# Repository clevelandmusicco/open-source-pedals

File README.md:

# Cleveland Music Co. Open Source Pedals

Here you can find the design files used in the production of [Cleveland Music Co.](https://clevelandmusicco.com) pedals. This includes schematics, PCB layouts, Gerber/BOM/CPL files for PCB fabrication and assembly, templates for enclosure drilling, and more. In addition to the sources we use for our retail pedals and kits, there are several DIY projects for popular so-called "clones" you can modify and/or fabricate on your own. All of these materials are made available as [Open Source Hardware](https://oshwa.org/resources/open-source-hardware-definition/) distributed under a [Creative Commons Attribution-ShareAlike 4.0 International license](https://creativecommons.org/licenses/by-sa/4.0/).

&nbsp;&nbsp;&nbsp;&nbsp;&nbsp;&nbsp;&nbsp;&nbsp;&nbsp;&nbsp;

## What is here and how do I view or use it?

The directory structure is self-explanatory.

* Most schematics and PCB layouts were created with [Eagle 9.6.2](https://eagle-updates.circuits.io/downloads/latest.html), which is free for personal use (but not open source). Designs added in the future will likely be created in [KiCad](https://www.kicad.org/).
* The zipped Gerber files, BOM, and CPL files can be used as-is at [JLCPCB](https://jlcpcb.com/).
* Drill layouts for enclosures are formatted for use and stored at [Tayda Electronics](https://drill.taydakits.com/).

If there are any deviations from the above, the README file for each pedal points that out.

>[!IMPORTANT]
>All Cleveland Music Co. logos and trademarks have been removed from these source files. The artwork we use for our commercial products is also omitted. This is conventient because it creates a clean starting point for modification, but it also helps to avoid potential branding conflicts or confusion. 
>
>Use of Cleveland Music Co. trademarks, logos, or other branding on any hardware, software, or documentation (including design files) derived from these materials without express written consent from Cleveland Music Co. is not permitted. 

### `eagle` directory files

The `.sch` and `.brd` (schematic and board) files are included. Additionally, there is an `.lbr` (library) containing only the footprints required to view and manipulate the `.brd` layout.

**The PCB layouts mostly use SMD components, with a few exceptions:** As a rule of thumb, aluminum electrolytic capacitors used for power filtering are through-hole, as are potentiometers, LEDs, switches, and trimmers. Some designs include through-hole pads for silver mica "tone capacitors" or similiar. This is pointed out in each pedal's README file and component suggestions are provided.

_The Superior Overdrive `.brd` file loaded in Eagle. Note the Cleveland Music Co. branding and trademarks have been removed from the source files._

### `fabrication` directory files

The `.zip` containing Gerber files is ready-to-use at [JLCPCB](https://jlcpcb.com/). It might be compatible with other services, but we haven't tested it. Also included are verified and tested `BOM.csv` and `CPL.csv` files for PCBA (Printed Circuit Board Assembly) services at JLCPCB.

The BOMs follow a few general guidelines:

1. High-quality component manufacturers like TDK, onsemi, Texas Instruments, Murata, Samsung, and others are favored wherever possible.
2. Audio signal path capacitors use C0G or NP0 MLCC capacitors from JLCPCB's parts library wherever possible.
3. As C0G/NP0 SMD capacitors tend to be larger than their X7R equivalents, 1206 and 0805 footprints are common for audio signal path capacitors in the PCB layouts.
4. Some of the BOMs can get expensive at JLCPCB due to the use of many so-called ["extended" components](https://jlcpcb.com/help/article/pcb-assembly-faqs). Our retail pedals and kits always use the highest-quality available components where it makes sense. If you want less expensive PCBs, use less expensive "basic" parts from the JLCPCB parts library, or source and solder the components yourself.

_Rendering of a Cleveland Music Co. Superior Overdrive PCB fabricated with these files. Note the Cleveland Music Co. branding and trademarks have been removed from the source files._

There is also a `.url` file with a link to the Drill Template at Tayda. These templates have been verified and tested. For example, [here is the Superior Overdrive Drill Template](https://drill.taydakits.com/box-designs/new?public_key=SVhxKzdDNXZjeXVUNXpSM1phNTFkdz09Cg==).

_The Superior Overdrive Drill Template at Tayda Electronics._

## What is [Open Source Hardware](https://oshwa.org/resources/open-source-hardware-definition/)?

Open source hardware is hardware whose design is made publicly available so that anyone can study, modify, distribute, make, and sell the design or hardware based on that design. The hardware’s source, the design from which it is made, is available in the preferred format for making modifications to it. Ideally, open source hardware uses readily-available components and materials, standard processes, open infrastructure, unrestricted content, and open-source design tools to maximize the ability of individuals to make and use hardware. Open source hardware gives people the freedom to control their technology while sharing knowledge and encouraging commerce through the open exchange of designs.

## In a nutshell, what is the [Creative Commons Attribution-ShareAlike 4.0 International license](https://creativecommons.org/licenses/by-sa/4.0/)?

### You are free to:

* **Share** — copy and redistribute the material in any medium or format for any purpose, even commercially.
* **Adapt** — remix, transform, and build upon the material for any purpose, even commercially.

### Under the following terms:

* **Attribution** — You must give appropriate credit, provide a link to the license, and indicate if changes were made. You may do so in any reasonable manner, but not in any way that suggests Cleveland Music Co. endorses you or your use.
* **ShareAlike** — If you remix, transform, or build upon the material, you must distribute your contributions under the same license as the original.
* **No additional restrictions** — You may not apply legal terms or technological measures that legally restrict others from doing anything the license permits.

We cannot revoke these freedoms as long as you follow the license terms, even if we decide to stop distributing these materials under the terms at a later date.

>[!WARNING]
>No warranties are given. The license may not give you all of the permissions necessary for your intended use. For example, other rights such as publicity, privacy, or moral rights may limit how you use these materials.

>[!CAUTION]
>This description highlights only some of the key features and terms of [the actual license](https://creativecommons.org/licenses/by-sa/4.0/). It is not a license and has no legal value. You should carefully review all of the terms and conditions of [the actual license](https://creativecommons.org/licenses/by-sa/4.0/) before using the contents of this repository.

## Why would a for-profit company do this? Are you worried about people "ripping you off"?

Basically, two ideas we fiercely support:

1. Sharing designs promotes innovation. Designers don't waste brain power "reinventing the wheel" when they can freely reuse and improve upon public designs.
2. People should have the right to study, modify, AND REPAIR the physical devices they own. And if people do not or cannot buy our hardware products for any reason, the should have _permission_ to make, sell, and distribute new designs or hardware derived from ours, as long as their work is also publicly shared.

We're not worried about people "ripping us off". Practically speaking, even with access to a product’s design, it's not trivial for someone else to make and sell it. They still need to source components, manufacture and/or assemble parts, design and implement a testing strategy, create distribution and commerce channels, and much more. We have a head start doing all of this while offering our products at prices low enough that it's likely not worth undercutting us. And frankly, if people really wanted to rip us off, they would reverse engineer and reproduce our products _whether they were open source or not_, selling them at higher "prestige" prices. Legally speaking, this would not make them criminals; it would just make them assholes.

So, as a matter of principle, we're happy to accept the risks posed by bad actors as the price to make knowledge and freedoms available to the good ones (such as yourself).

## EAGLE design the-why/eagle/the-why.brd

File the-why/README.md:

# The 'Why'

The 'Why' is an adaptation of the venerable Electro-Harmonix (EHX) Big Muff circuit. All components are surface mount (SMD) except for the power filtering capacitor and three board-mounted pots. So, assembly is as simple as soldering these four parts to the PCB.

## Big Muff Circuit Variation

The Big Muff is famous for its many different variants over the years, each having a unique sound due to its mix of component values, transistor types and current gain (hFE), and even the dielectrics of the capacitors. Since the topology of the schematic is consistent, the same PCB layout can be used to make (almost) any variant. So, fabricating a "Ram's Head" as opposed to a "Green Russian", for example, is a matter of editing the BOM. I have made no fewer than five great-sounding Big Muffs using the files in this directory, with some of them being mashups of values from several different variants (the [Cleveland Music Co. Smuffle Fuzz](https://clevelandmusicco.com/pedals/smuffle-fuzz/) is one such example).

The canonical source for Big Muff schematics has to be [Kit Rae's Big Muff Page](https://www.kitrae.net/music/music_big_muff.html). Here you can find a schematic for every known variant of the Big Muff circuit with consistent part identifiers and notes about capacitor dialectrics, transistors, etc.

To make it easy to fab different variants, I have used the same identifiers Kit uses on his website. The schematic in the `eagle` directory is from [the David Gilmour Big Muff](https://www.kitrae.net/music/David_Gilmour_Big_Muff.html) (which Kit calls "Version 2 Big Muff 1973 #3"), and `BOM_gilmour.csv` specifies JLC part numbers that match this schematic. It sounds really, really good. If you want to make a different variant, simply create a new BOM selecting parts that match the schematic of you choice.

`BOM_gilmour.csv` specifies fairly low-hFE [MMBT3904 transistors](https://jlcpcb.com/partdetail/21237-MMBT3904_RANGE_100_300/C20526). I think they sound great in this variant, but hFE on Big Muff transistors varies wildly. Do some reading at Kit's page and tweak as you see fit.

>[!NOTE]
> I'll add more BOMs in the future; especially the variants that are most often cloned. Pull requests are also welcome! The only reason I haven't added more already is that most of mine use parts that aren't in the public JLC Parts Library ¯\\_(ツ)_/¯

You may occasionally need to change a capacitor footprint to use the part number you want (the 0603 C8 is probably the leading candidate here; I happen to have a large number of C0G 0603 caps in my personal parts library). The largest footprint in `the-why.lbr` is 1206; there's plenty of space on the board to make all capacitors 1206 if you wanted to. You won't even need to change the CPL coordinates if you're careful.

## Through-hole Component Suggestions

| Qty | URL | Description | Notes |
| --- | --- | --- | --- |
| 3 | [Tayda SKU A-2907](https://www.taydaelectronics.com/b-100k-ohm-linear-taper-potentiometer-with-pc-mount.html) | B100K OHM Linear Taper Potentiometer PC Mount | I typically use A100K for SUSTAIN and VOLUME |
| 1 | [Mouser PN 667-EEU-FR1E101B](https://www.mouser.com/ProductDetail/667-EEU-FR1E101B) | Use whatever low-ESR cap you prefer |

## A Few Words About SMD/SMT Hate

Get over it. If you want to make an exact clone of a 1969 Big Muff Pi V1, best of luck to you; The 'Why' is probably not a project for you. The 'Why' _is_ for Muffheads who want to learn about SMT PCBA, are intrigued or at least aren't bothered by it, or just can't be arsed to source and solder through-hole components.

Sure, SMT is more difficult (if not impossible) to repair sometimes. And, yeah, such tiny parts must _sound different_ than big, magical, 'mojo' parts, right? Of course they do. But the same could be said for every part in every version of the Big Muff that ever used different capacitor dielectrics or resistor material or paint colour or whatever. An NP0 MLCC SMD capacitor performs differently than a polyester film cap. Obviously. But different isn't the same as inferior.

Also consider that component tolerances can make ten Big Muffs that came off the line back-to-back in 1974 all sound slightly different, even when brand new. Going by the values on a schematic will not get you an exact copy of the holy grail sound you might think you're seeking. Many of the critical components used were often well out of the specified tolerance in the first place, and as the parts age, those values drift even further.

(Let's not talk about 'fidelity', either. The purpose of distortion devices like the Big Muff is literally to _distort (pull or twist out of shape)_ an audio signal. Come on, man.)

So, if you know what you're doing and you select capacitor dielectrics that make sense, pay attention to transistor current gain, and so on, you can make a perfectly-legitimate, excellent-sounding (and often far less noisy) Big Muff with SMT.

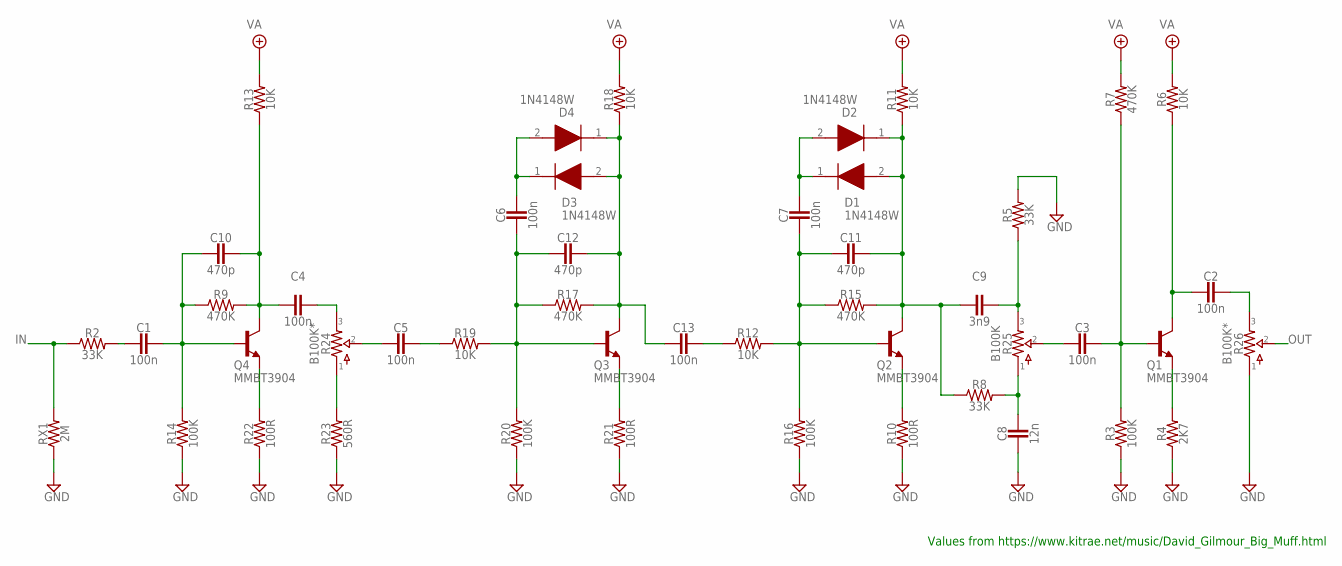
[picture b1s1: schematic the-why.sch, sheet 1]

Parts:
C1, C2, C3, C4, C5, C6, C7, C13: 100n; RESISTOR_C1206
C8: 12n; RESISTOR_R0603
C9: 3n9; RESISTOR_C1206
C10, C11, C12: 470p; RESISTOR_R0603
D1, D2, D3, D4: 1N4148W; SODFL3816X120N
Q1, Q2, Q3, Q4: MMBT3904; TRANSISTOR_SOT23-BEC
R2, R5, R8: 33K; RESISTOR_R0603
R3, R14, R16, R20: 100K; RESISTOR_R0603
R4: 2K7; RESISTOR_R0603
R6, R11, R12, R13, R18, R19: 10K; RESISTOR_R0603
R7, R9, R15, R17: 470K; RESISTOR_R0603
R10, R21, R22: 100R; RESISTOR_R0603
R23: 560R; RESISTOR_R0603
R24, R26: B100K*; 16MM_B.MOUNT
R25: B100K; 16MM_B.MOUNT
RX1: 2M; RESISTOR_R0603

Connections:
GND: C8.2, R3.1, R4.1, R5.2, R10.1, R14.1, R16.1, R20.1, R21.1, R22.1, R23.1, R26.1, RX1.1; also elsewhere on the board
IN: R2.1, RX1.2; also elsewhere on the board
unnamed: C1.2, R2.2
unnamed: C1.1, C10.2, Q4.B, R9.1, R14.2
unnamed: C4.2, C10.1, Q4.C, R9.2, R13.1
unnamed: Q4.E, R22.2
unnamed: C4.1, R24.3
unnamed: R23.2, R24.1
unnamed: C5.2, R24.2
unnamed: C5.1, R19.1
unnamed: C6.2, C12.2, Q3.B, R17.1, R19.2, R20.2
unnamed: C6.1, D3.1 (K), D4.2 (A)
unnamed: Q3.E, R21.2
unnamed: C9.1, R5.1, R25.3
unnamed: C13.1, R12.1
unnamed: C7.2, C11.2, Q2.B, R12.2, R15.1, R16.2
unnamed: Q2.E, R10.2
unnamed: C7.1, D1.1 (K), D2.2 (A)
unnamed: C8.1, R8.2, R25.1
unnamed: C3.2, R25.2
unnamed: C3.1, Q1.B, R3.2, R7.1
unnamed: Q1.E, R4.2
unnamed: C2.2, Q1.C, R6.1
unnamed: C2.1, R26.3
unnamed: C12.1, C13.2, D3.2 (A), D4.1 (K), Q3.C, R17.2, R18.1
unnamed: C9.2, C11.1, D1.2 (A), D2.1 (K), Q2.C, R8.1, R11.1, R15.2
OUT: R26.2; also elsewhere on the board
VA: R6.2, R7.2, R11.2, R13.2, R18.2; also elsewhere on the board

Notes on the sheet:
Values from https://www.kitrae.net/music/David_Gilmour_Big_Muff.html

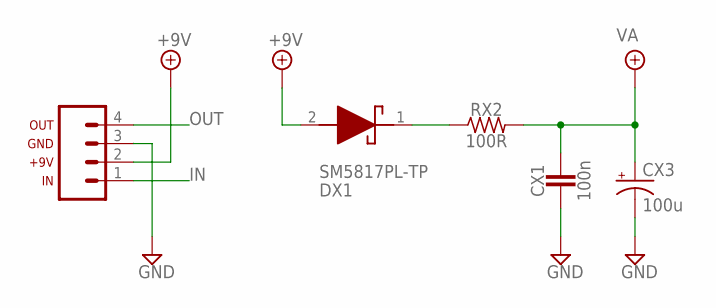
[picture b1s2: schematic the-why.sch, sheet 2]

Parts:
CX1: 100n; RESISTOR_R0603
CX3: 100u; 063_025
DX1: SM5817PL-TP; SOD3716X120N
J101: 1X04_SMD_STRAIGHT_COMBO; 1X04
RX2: 100R; RESISTOR_R0603

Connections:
+9V: DX1.2 (A), J101.2 (+9V)
GND: CX1.2, CX3.-, J101.3 (GND); also elsewhere on the board
IN: J101.1 (IN); also elsewhere on the board
unnamed: DX1.1 (K), RX2.1
OUT: J101.4 (OUT); also elsewhere on the board
VA: CX1.1, CX3.+, RX2.2; also elsewhere on the board

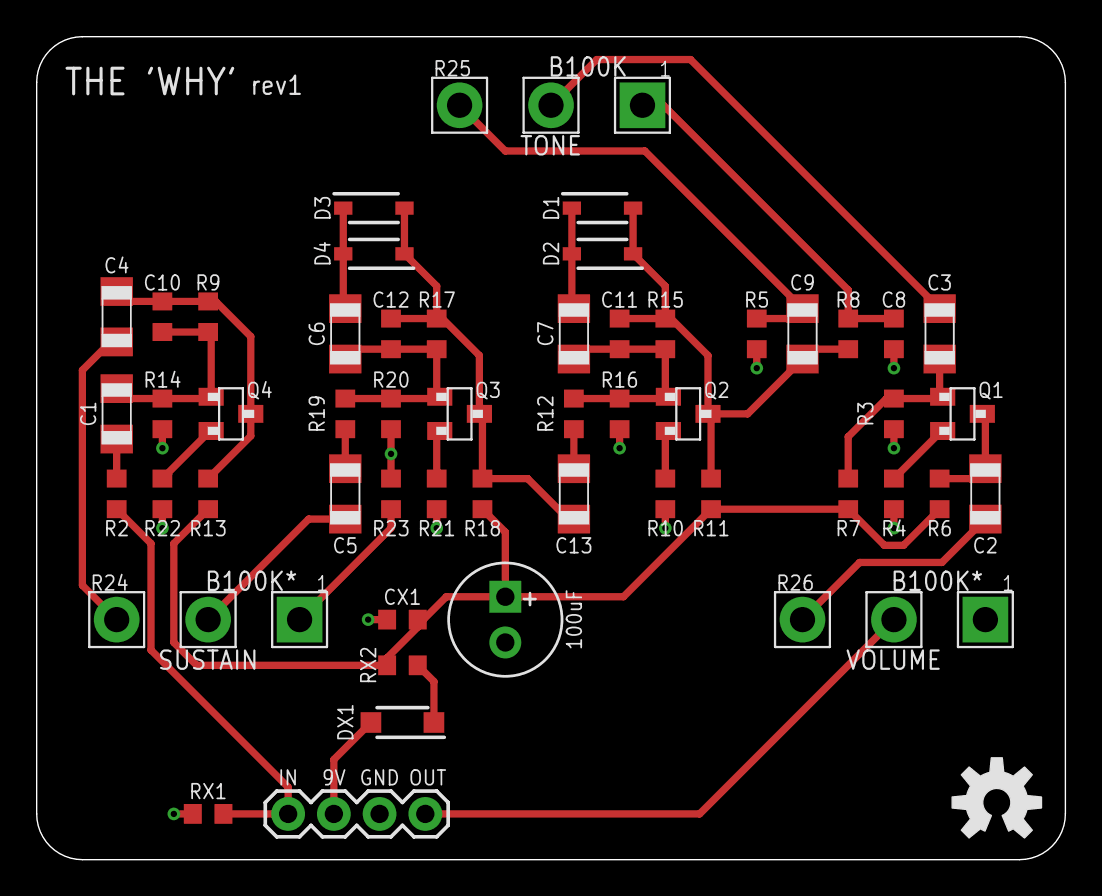
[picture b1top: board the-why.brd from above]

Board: 2 copper layers, 57.1 x 45.7 mm, 54 parts (0 on the bottom side), 30 nets.

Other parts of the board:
U$1: 125B_BOARD
U$2: OSHW-LOGO-M

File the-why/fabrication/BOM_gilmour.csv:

Comment,Designator,Footprint,JLCPCB Part #（optional）
100n,C1,CAP_C1206,C338082
100n,C2,CAP_C1206,C338082
100n,C3,CAP_C1206,C338082
100n,C4,CAP_C1206,C338082
100n,C5,CAP_C1206,C338082
100n,C6,CAP_C1206,C338082
100n,C7,CAP_C1206,C338082
12n,C8,CAP_C0603,C2178767
3n9,C9,CAP_C1206,C541503
470p,C10,CAP_C0603,C27694
470p,C11,CAP_C0603,C27694
470p,C12,CAP_C0603,C27694
100n,C13,CAP_C1206,C338082
100n,CX1,CAP_C0603,C14663
1N4148W,D1,SODFL3816X120N,C81598
1N4148W,D2,SODFL3816X120N,C81598
1N4148W,D3,SODFL3816X120N,C81598
1N4148W,D4,SODFL3816X120N,C81598
SM5817PL-TP,DX1,SOD3716X120N,C7420328
MMBT3904,Q1,TRANSISTOR_SOT23-BEC,C20526
MMBT3904,Q2,TRANSISTOR_SOT23-BEC,C20526
MMBT3904,Q3,TRANSISTOR_SOT23-BEC,C20526
MMBT3904,Q4,TRANSISTOR_SOT23-BEC,C20526
33K,R2,RESISTOR_R0603,C4216
100K,R3,RESISTOR_R0603,C25803
2K7,R4,RESISTOR_R0603,C13167
33K,R5,RESISTOR_R0603,C4216
10K,R6,RESISTOR_R0603,C25804
470K,R7,RESISTOR_R0603,C23178
33K,R8,RESISTOR_R0603,C4216
470K,R9,RESISTOR_R0603,C23178
100R,R10,RESISTOR_R0603,C22775
10K,R11,RESISTOR_R0603,C25804
10K,R12,RESISTOR_R0603,C25804
10K,R13,RESISTOR_R0603,C25804
100K,R14,RESISTOR_R0603,C25803
470K,R15,RESISTOR_R0603,C23178
100K,R16,RESISTOR_R0603,C25803
470K,R17,RESISTOR_R0603,C23178
10K,R18,RESISTOR_R0603,C25804
10K,R19,RESISTOR_R0603,C25804
100K,R20,RESISTOR_R0603,C25803
100R,R21,RESISTOR_R0603,C22775
100R,R22,RESISTOR_R0603,C22775
560R,R23,RESISTOR_R0603,C23204
2M,RX1,RESISTOR_R0603,C22976
100R,RX2,RESISTOR_R0603,C22775

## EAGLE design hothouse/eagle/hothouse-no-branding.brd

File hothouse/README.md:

# Hothouse Digital Signal Processing Pedal (125B)

The Hothouse is a compact effect pedal for the [Electrosmith Daisy Seed](https://electro-smith.com/products/daisy-seed). You can use it to easily get Daisy Seed DSP projects off the breadboard and onto your pedalboard, either by compiling and flashing any of the code in [the official repository](https://github.com/clevelandmusicco/HothouseExamples), or by using the [Daisy Web Programmer](https://electro-smith.github.io/Programmer/) with the [pre-compiled binaries](https://github.com/clevelandmusicco/HothouseExamples/releases). And of course, you can also [write your own DSP code for the Hothouse](https://github.com/clevelandmusicco/HothouseExamples/wiki/Creating-your-own-effects). Basically, anything that runs on the Daisy Seed will run on the Hothouse.

This directory contains the open source hardware files for the [Cleveland Music Co. Hothouse DSP Pedal Kit](https://clevelandmusicco.com/hothouse-diy-digital-signal-processing-platform-kit/). Included are the gerber, BOM, and CPL files required to fabricate your own PCBs at JLCPCB. Also included are suggestions for the various through-hole components and other hardware required.

>[!NOTE]
> No step-by-step tutorial for having the boards fabricated is provided. It's assumed that anyone interested in using these files is already familiar with the fabrication process at their provider of choice. However, the files in this repo have only been tested with JLCPCB.

>[!IMPORTANT]
> Remember that all of these materials are made available as [Open Source Hardware](https://oshwa.org/resources/open-source-hardware-definition/) distributed under a [Creative Commons Attribution-ShareAlike 4.0 International license](https://creativecommons.org/licenses/by-sa/4.0/). Before using these materials, be sure to follow the links above and read the [main repo README](/README.md) and [LICENSE](/LICENSE) files.

## Overview

The Hothouse design is comprised of three PCBs:

1. The Main PCB,
2. A Switching & LED daughterboard,
3. A Power & Audio I/O daughterboard.

_The Main PCB_

_The Switching & LED Daughterboard_

_The Power & Audio I/O Daughterboard_

The main PCB is designed for a mix of through-hole and surface-mount components, while the two daughterboards use only through-hole components. The three PCBs are connected by 6-pin ribbon cables. Refer to [the commercial product build docs](https://github.com/clevelandmusicco/HothouseExamples/wiki/Cleveland-Music-Co.-Hothouse-DIY-Digital-Signal-Processing-Pedal-Kit-Build-Guide-(Stereo-Version)) for more information.

All commercial branding (Cleveland Music Co.-specific stuff) has been removed from the PCBs and files in this repository.

### eagle Directory

For each of the three boards, you will find four files:

* An Eagle schematic (`.sch`)
* An Eagle board (`.brd`)
* An Eagle library (`.lbr`) for the devices and footprints specific to the board layout
* A PDF schematic

All the files were created with Eagle 9.6.2 "free". Having separate files for each board provides flexibility; not everyone will want to modify or fab all three PCBs.

### fabrication Directory

There is a zip of the gerber files for each board following the same naming convention as the `eagle` directory. A BOM and CPS file in `.csv` and `.xls` formats is provided for use with `hothouse-no-branding.zip`. You'll also find a DIY drill template in `.pdf` format for those wanting to drill their own 125B enclosures.

## Resources

* [HothouseExamples GitHub repo](https://github.com/clevelandmusicco/HothouseExamples) - The official code examples repo with effects created in C++, Puredata/Plugdata, and Max.
* [Cleveland Music Co. Hothouse DSP Pedal Kit](https://clevelandmusicco.com/hothouse-diy-digital-signal-processing-platform-kit/) - A retail example of a pedal created from the files in this directory. _The chicken or the egg?_ and all that ...
* [Cleveland Music Co. Hothouse Build Guide](https://github.com/clevelandmusicco/HothouseExamples/wiki/Cleveland-Music-Co.-Hothouse-DIY-Digital-Signal-Processing-Pedal-Kit-Build-Guide-(Stereo-Version)) - The build documentation for the retail kit.
* [DIY 125B enclosure drill template](fabrication/hothouse-drill-template.pdf) - For those wanting to drill their own 125B enclosures. It assumes you assemble everything according to the build guide above for proper fit.
* [Tayda 125B drill template](https://drill.taydakits.com/box-designs/new?public_key=Q2luT1FRTVZRM3Bab01YbXd3eituUT09Cg==) - For custom-machined enclosures from Tayda. Highly-recommended if you don't have a drill press or some other way to accurately drill holes in the TOP and SIDES of an enclosure. (You'll need to sign up for an account; FWIW, I've never recieved a single spam email from them.)

## Bill Of Materials

`BOM.xls` (or `BOM.csv`) specifies the surface-mount components. It is adapted from a late-2025 fabrication run used for the commercial kits. "Adapted" because some of the parts used aren't always in stock at JLCPCB publicly (they are stocked in my personal parts library); several components have been swapped out here for purposes of general availability.

Budget-friendly through-hole components to complete the build and some sourcing suggestions:

| QTY | SOURCE URL | DESCRIPTION | NOTES |
| :---: | :--- | :--- | :--- |
| 2 | [Tayda SKU: A-1310](https://www.taydaelectronics.com/20-pin-2-54-mm-single-row-female-pin-header.html) | 20 Pin 2.54mm Single Row Female Pin Header | |
| 3 | [Tayda SKU: A-3670](https://www.taydaelectronics.com/mini-toggle-switch-1m-series-spdt-on-off-on-short-lever.html) | Toggle SPDT On-Off-On Short Lever | |
| 2 | [Tayda SKU: A-4807](https://www.taydaelectronics.com/spst-momentary-soft-touch-push-button-stomp-foots-pedal-switch-on-off-b.html) | SPST Momentary Soft-Touch Push-Button Stomp Switch OFF-(ON) | |
| 6 | [Tayda SKU: A-2969](https://www.taydaelectronics.com/b10k-ohm-linear-taper-potentiometer-round-shaft-pc-mount-l.html) | 10K OHM Linear Taper Potentiometer PCB Mount Round Shaft Dia: 6.35mm | Use whatever 16mm pot you prefer |
| 3 | [Tayda SKU: A-5527](https://www.taydaelectronics.com/dust-seal-covers-for-potentiometer.html) | Dust Seal Cover For Potentiometer | Could also use electrical tape |
| 2 | [Tayda SKU: A-261](https://www.taydaelectronics.com/led-3mm-red.html) | LED 3mm Red | |
| 1 | [Tayda SKU: A-4118](https://www.taydaelectronics.com/dc-power-jack-2-1mm-barrel-type-pcb-mount.html) | DC Power Jack 2.1mm Barrel-Type PCB Mount | The retail kits use a Kobiconn jack, but this works fine |
| 6 | [Tayda SKU: A-932](https://www.taydaelectronics.com/91640-dup-knob-davies-1900h-clone-black.html) | Knob DAVIES 1900H CLONE Black | Or anything that fits the shafts of the pots you're using |
| 1 | [Tayda SKU: A-6628](https://www.taydaelectronics.com/matte-white-sand-texture-125b-style-aluminum-diecast-enclosure.html) | 125B Style Aluminum Diecast Enclosure MATTE WHITE SAND TEXTURE | Colour or finish isn't important; this is just what the retail kits use |
| 1 | [Tayda SKU: A-5165-CST-DR1](https://www.taydaelectronics.com/125b-custom-drill-enclosure-service.html) | 125B ENCLOSURE CUSTOM DRILL SERVICE | Optional |
| 1 | [Tayda SKU: A-5165-CST-UV1](https://www.taydaelectronics.com/125b-uv-printing-service.html) | 125B ENCLOSURE FACE UV PRINTING SERVICE | Optional |
| 1 | [Stompbox Parts SKU: RIB-6P-1](https://stompboxparts.com/cables-wire-plugs/ribbon-cable-6-pin-1-prebond/) | Ribbon Cable - 6 pin - 1" - Prebond | _Prebond_ is important! But you could also simply "fly" 6 hookup wires the olde fashioned way |
| 1 | [Stompbox Parts SKU: RIB-6P-2](https://stompboxparts.com/cables-wire-plugs/ribbon-cable-6-pin-2-prebond/) | Ribbon Cable - 6 pin - 2" - Prebond | Ditto above|
| 2 | [Mouser PN: 568-NRJ6HM1](https://www.mouser.com/ProductDetail/568-NRJ6HM1)| Neutrik NRJ6HM-1 1/4" Stereo Audio Connector | [Tayda SKU: A-6446](https://www.taydaelectronics.com/6-35mm-1-4-stereo-insulated-switched-cylindrical-socket-jack-pcb-pins.html) also works in a pinch; but the Neutrik part is recommended |
| 2 | [Mouser PN: 568-NRJ6HM1](https://www.mouser.com/ProductDetail/568-NRJ-NUT-MN)| Neutrik NRJ-NUT-MN Mounting Nut for NRJ6HM-1 | |
| 1 | [Mouser PN: 667-EEU-FR1E101B](https://www.mouser.com/ProductDetail/667-EEU-FR1E101B)| Panasonic EEU-FR1E101B Aluminum Electrolytic Capacitors - Radial Leaded 25VDC 100uF 6.3x11.2mm LS 5.0mm | Use whatever low-ESR capacitor you prefer |

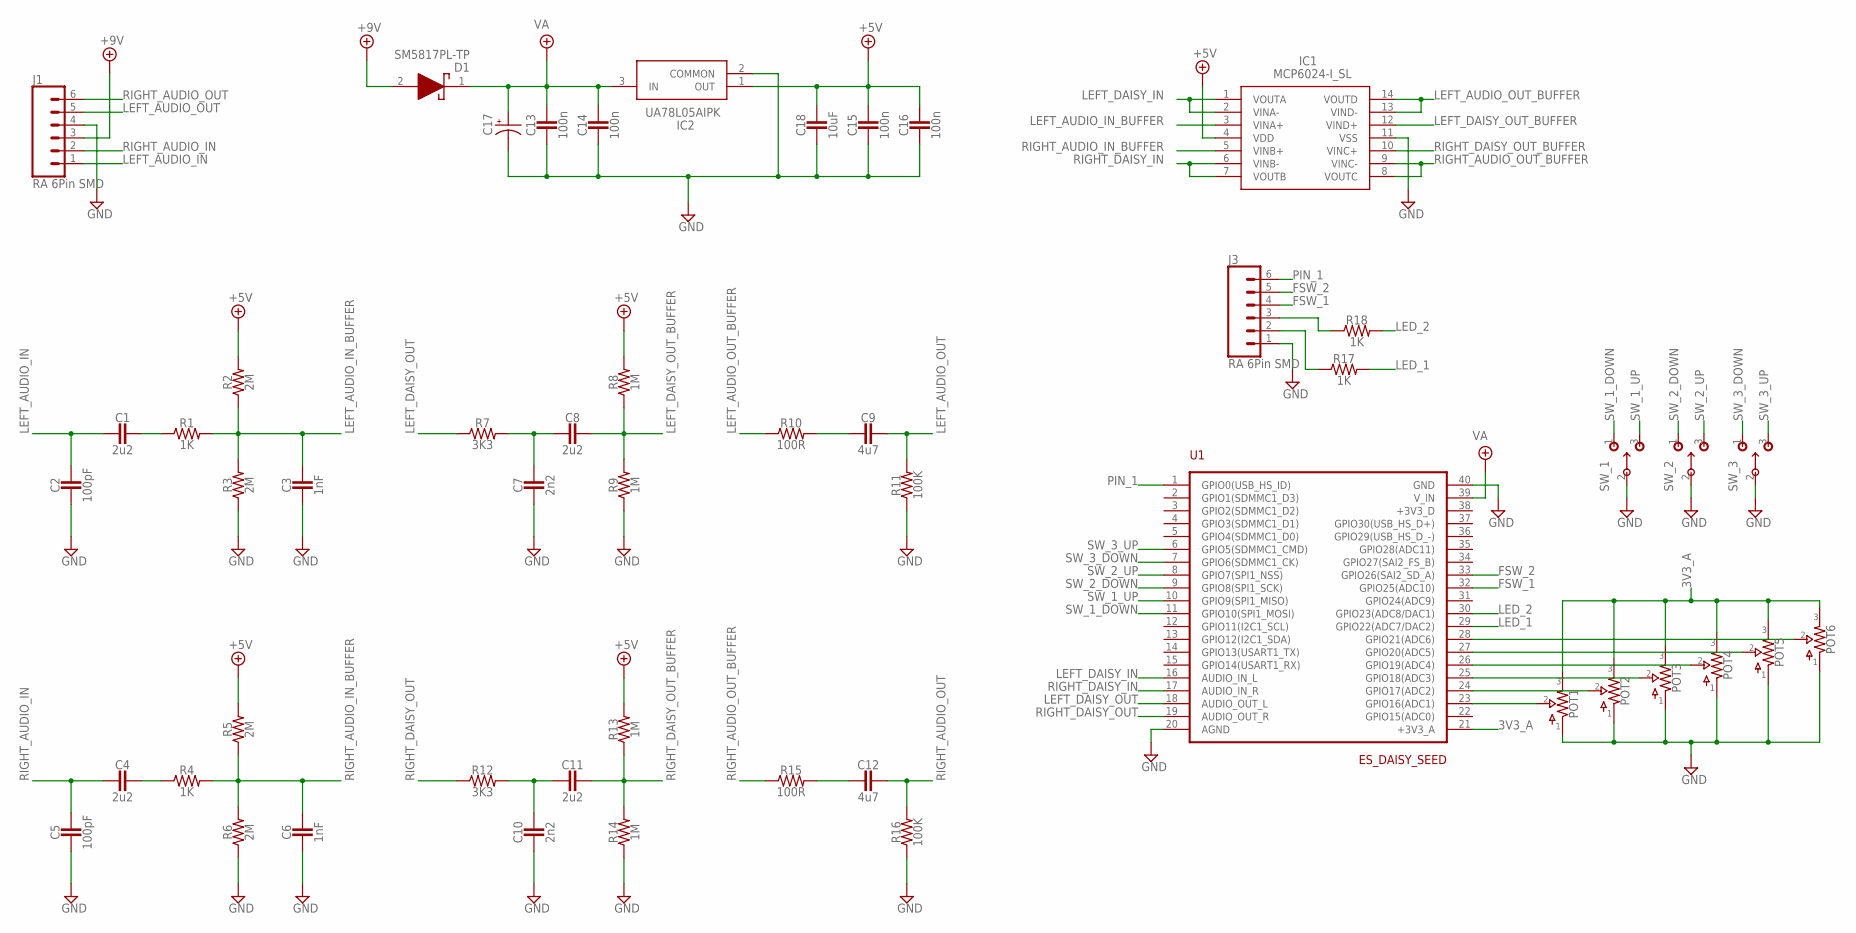
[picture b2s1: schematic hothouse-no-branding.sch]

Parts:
C1, C4, C8, C11: 2u2; RESISTOR_C1206
C2, C5: 100pF; RESISTOR_R0603
C3, C6: 1nF; RESISTOR_R0603
C7, C10: 2n2; RESISTOR_R0603
C9, C12: 4u7; RESISTOR_C1206
C13, C14, C15, C16: 100n; RESISTOR_C0805
C17: 0631; 063_025
C18: 10uF; RESISTOR_C0805
D1: SM5817PL-TP; SOD3716X120N
IC1: MCP6024-I_SL; SOIC127P600X175-14N
IC2: UA78L05AIPK; PK(R-PSSO-F3)
J1, J3: RA 6Pin SMD; 1X06
POT1, POT2, POT3, POT4, POT5, POT6: 16MM.1; 16MM_B.MOUNT
R1, R4, R17, R18: 1K; RESISTOR_R0603
R2, R3, R5, R6: 2M; RESISTOR_R0603
R7, R12: 3K3; RESISTOR_R0603
R8, R9, R13, R14: 1M; RESISTOR_R0603
R10, R15: 100R; RESISTOR_R0603
R11, R16: 100K; RESISTOR_R0603
SW_1, SW_2, SW_3: SPDT.LUGS
U1: ES_DAISY_SEED

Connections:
3V3_A: POT1.3, POT2.3, POT3.3, POT4.3, POT5.3, POT6.3, U1.21 (+3V3_A)
+5V: C15.1, C16.1, C18.1, IC1.4 (VDD), IC2.1 (OUT), R2.2, R5.2, R8.2, R13.2
+9V: D1.2 (A), J1.3
FSW_1: J3.4, U1.32 (GPIO25(ADC10))
FSW_2: J3.5, U1.33 (GPIO26(SAI2_SD_A))
GND: C2.2, C3.2, C5.2, C6.2, C7.2, C10.2, C13.2, C14.2, C15.2, C16.2, C17.-, C18.2, IC1.11 (VSS), IC2.2 (COMMON), J1.4, J3.1, POT1.1, POT2.1, POT3.1, POT4.1, POT5.1, POT6.1, R3.1, R6.1, R9.1, R11.1, R14.1, R16.1, SW_1.2, SW_2.2, SW_3.2, U1.20 (AGND), U1.40 (GND)
LED_1: R17.2, U1.29 (GPIO22(ADC7/DAC2))
LED_2: R18.2, U1.30 (GPIO23(ADC8/DAC1))
LEFT_AUDIO_IN: C1.2, C2.1, J1.1
LEFT_AUDIO_IN_BUFFER: C3.1, IC1.3 (VINA+), R1.2, R2.1, R3.2
LEFT_AUDIO_OUT: C9.1, J1.5, R11.2
LEFT_AUDIO_OUT_BUFFER: IC1.13 (VIND-), IC1.14 (VOUTD), R10.1
LEFT_DAISY_IN: IC1.1 (VOUTA), IC1.2 (VINA-), U1.16 (AUDIO_IN_L)
LEFT_DAISY_OUT: R7.1, U1.18 (AUDIO_OUT_L)
LEFT_DAISY_OUT_BUFFER: C8.1, IC1.12 (VIND+), R8.1, R9.2
unnamed: C4.1, R4.1
unnamed: C1.1, R1.1
unnamed: POT1.2, U1.23 (GPIO16(ADC1))
unnamed: C10.1, C11.2, R12.2
unnamed: C12.2, R15.2
unnamed: POT2.2, U1.24 (GPIO17(ADC2))
unnamed: C7.1, C8.2, R7.2
unnamed: POT3.2, U1.25 (GPIO18(ADC3))
unnamed: POT4.2, U1.26 (GPIO19(ADC4))
unnamed: POT5.2, U1.27 (GPIO20(ADC5))
unnamed: POT6.2, U1.28 (GPIO21(ADC6))
unnamed: J3.3, R18.1
unnamed: C9.2, R10.2
unnamed: J3.2, R17.1
PIN_1: J3.6, U1.1 (GPIO0(USB_HS_ID))
RIGHT_AUDIO_IN: C4.2, C5.1, J1.2
RIGHT_AUDIO_IN_BUFFER: C6.1, IC1.5 (VINB+), R4.2, R5.1, R6.2
RIGHT_AUDIO_OUT: C12.1, J1.6, R16.2
RIGHT_AUDIO_OUT_BUFFER: IC1.8 (VOUTC), IC1.9 (VINC-), R15.1
RIGHT_DAISY_IN: IC1.6 (VINB-), IC1.7 (VOUTB), U1.17 (AUDIO_IN_R)
RIGHT_DAISY_OUT: R12.1, U1.19 (AUDIO_OUT_R)
RIGHT_DAISY_OUT_BUFFER: C11.1, IC1.10 (VINC+), R13.1, R14.2
SW_1_DOWN: SW_1.1, U1.11 (GPIO10(SPI1_MOSI))
SW_1_UP: SW_1.3, U1.10 (GPIO9(SPI1_MISO))
SW_2_DOWN: SW_2.1, U1.9 (GPIO8(SPI1_SCK))
SW_2_UP: SW_2.3, U1.8 (GPIO7(SPI1_NSS))
SW_3_DOWN: SW_3.1, U1.7 (GPIO6(SDMMC1_CK))
SW_3_UP: SW_3.3, U1.6 (GPIO5(SDMMC1_CMD))
VA: C13.1, C14.1, C17.+, D1.1 (K), IC2.3 (IN), U1.39 (V_IN)

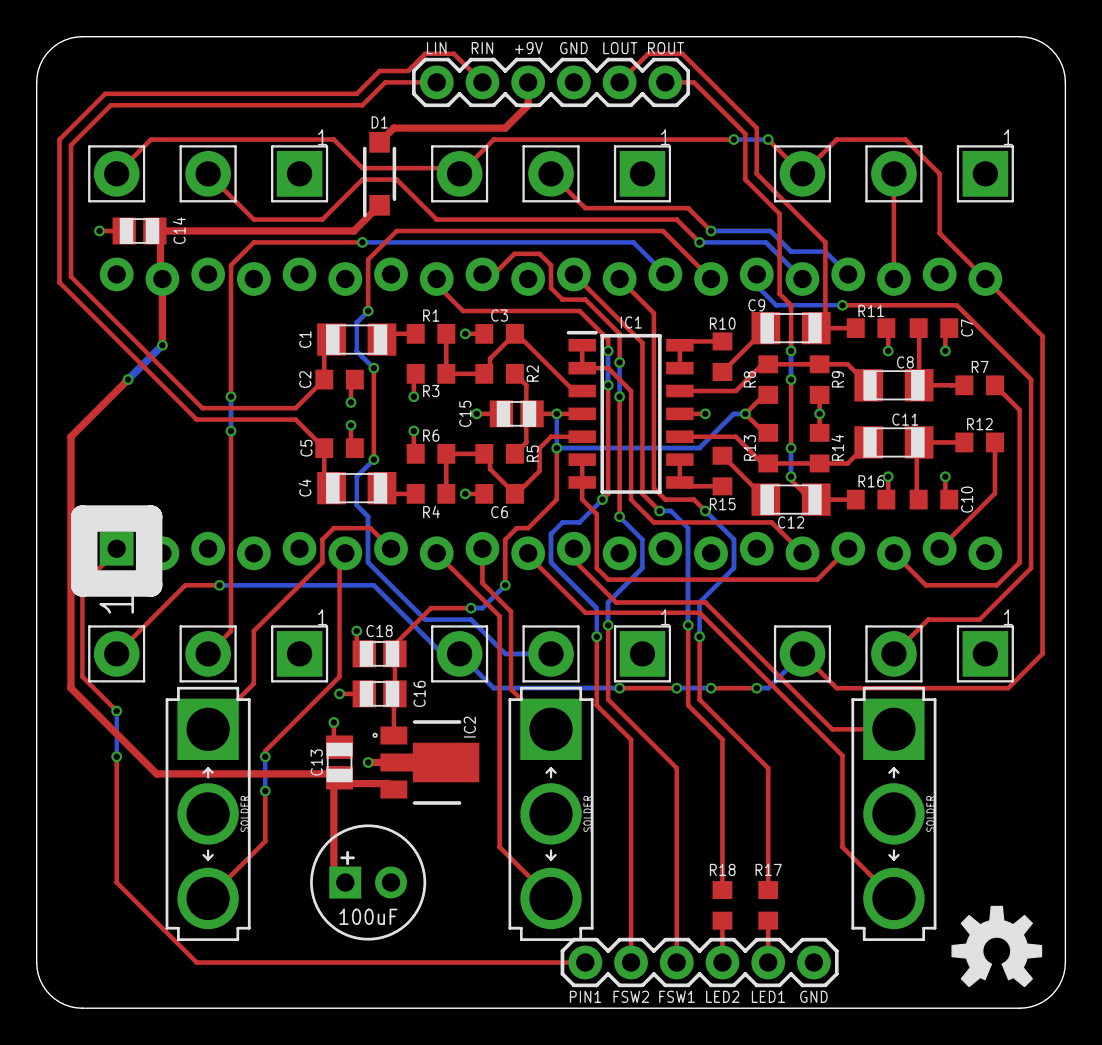
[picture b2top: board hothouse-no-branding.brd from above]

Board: 2 copper layers, 57.1 x 54.0 mm, 53 parts (0 on the bottom side), 44 nets.

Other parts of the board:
U$1: OSHW-LOGO-M
U$2: 125B_MULTI_DRILL

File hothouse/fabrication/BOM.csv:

Comment	Designator	Footprint	JLCPCB Part #
2u2	C4,C8,C1,C11	CAPACITOR_C1206	C50254
10uF	C18	CL21A106KAYNNNE	C15850
4u7	C12,C9	CAPACITOR_C1206	C29823
2n2	C10,C7	CAPACITOR_R0603	C1604
diode	D1	SM5817PL-TPSOD3716X120N	C669022
op-amp	IC1	MCP6024-I_SLSOIC127P600X175-14N	C43211
1nF	C6,C3	CAPACITOR_R0603	C1588
100n	C16,C13,C15,C14	CAPACITOR_C0805	C28233
voltagereg	IC2	UA78L05AIPKPK(R-PSSO-F3)	C507276
100R	R15,R10	RESISTOR_R0603	C22775
100pF	C5,C2	CAPACITOR_R0603	C14858
1M	R9,R13,R8,R14	RESISTOR_R0603	C22935
3K3	R12,R7	RESISTOR_R0603	C22978
1K	R17,R18,R4,R1	RESISTOR_R0603	C21190
100K	R11,R16	RESISTOR_R0603	C25803
2M	R5,R3,R2,R6	RESISTOR_R0603	C22976

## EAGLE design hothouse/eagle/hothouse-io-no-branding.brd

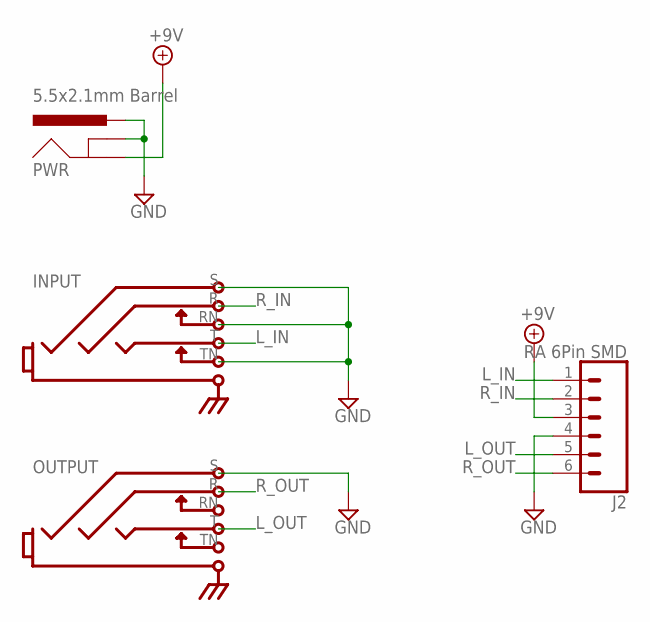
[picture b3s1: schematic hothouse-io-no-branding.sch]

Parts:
INPUT: STEREOSW2GND; NEUTRIK-NRJ6HM-1
J2: RA 6Pin SMD; 1X06
OUTPUT: STEREOSW2GND; NEUTRIK-NRJ6HM-1
PWR: 5.5x2.1mm Barrel; POWER_JACK_PTH_SLOT

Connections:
+9V: J2.3, PWR.GND
GND: INPUT.RN, INPUT.S, INPUT.TN, J2.4, OUTPUT.S, PWR.GNDBREAK, PWR.PWR
L_IN: INPUT.T, J2.1
L_OUT: J2.5, OUTPUT.T
R_IN: INPUT.R, J2.2
R_OUT: J2.6, OUTPUT.R

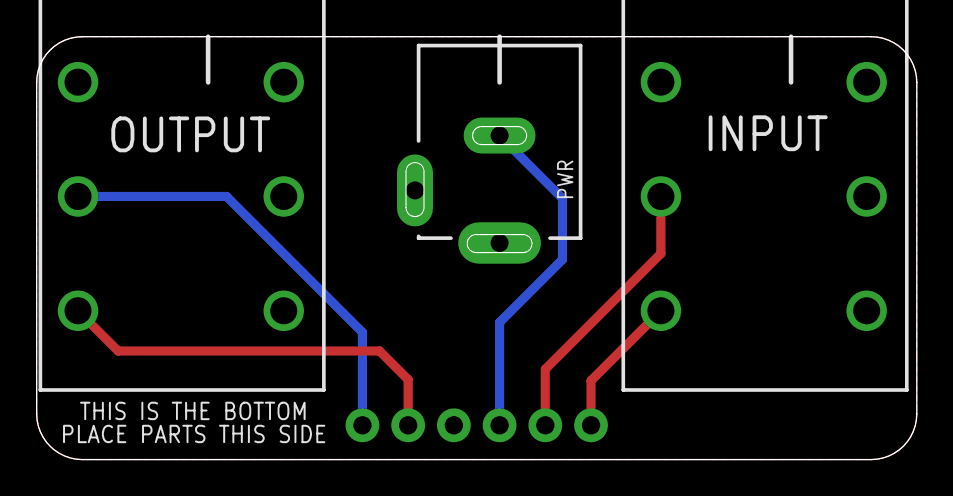
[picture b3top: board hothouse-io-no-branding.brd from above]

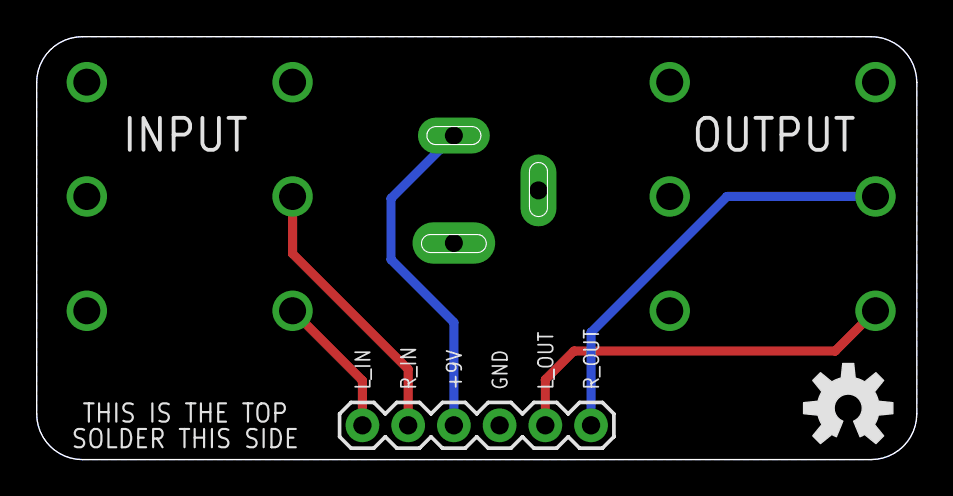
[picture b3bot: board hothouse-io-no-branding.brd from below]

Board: 2 copper layers, 48.9 x 23.5 mm, 5 parts (2 on the bottom side), 6 nets.

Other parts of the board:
U$1: OSHW-LOGO-M

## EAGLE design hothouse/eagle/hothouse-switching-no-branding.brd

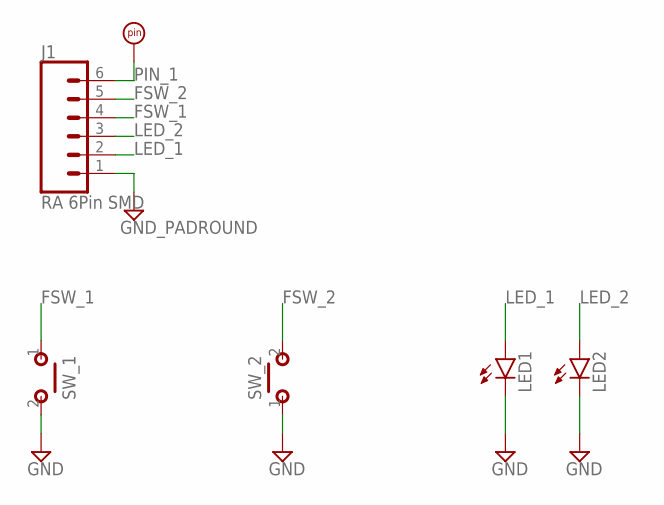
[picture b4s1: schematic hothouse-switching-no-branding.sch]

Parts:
GND2: GND_PADROUND; ROUND
J1: RA 6Pin SMD; 1X06
LED1, LED2: LED3MM
SW_1, SW_2: SPST.PBS.MOM
U$5: PADS.RND_NL; PAD2

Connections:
FSW_1: J1.4, SW_1.1
FSW_2: J1.5, SW_2.2 (S)
GND: GND2.1, J1.1, LED1.K (C), LED2.K (C), SW_1.2 (S), SW_2.1
LED_1: J1.2, LED1.A
LED_2: J1.3, LED2.A
PIN_1: J1.6, U$5.P$1

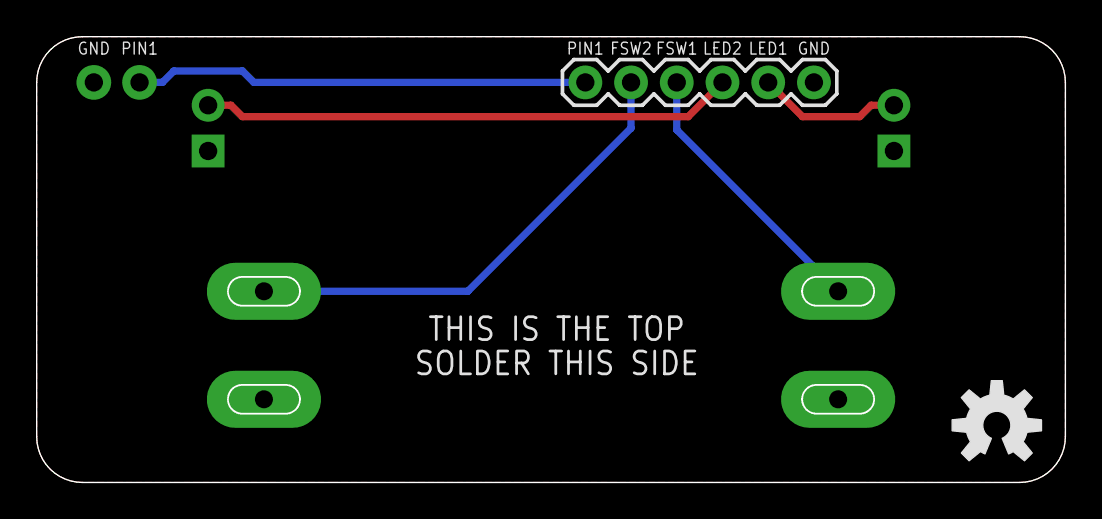
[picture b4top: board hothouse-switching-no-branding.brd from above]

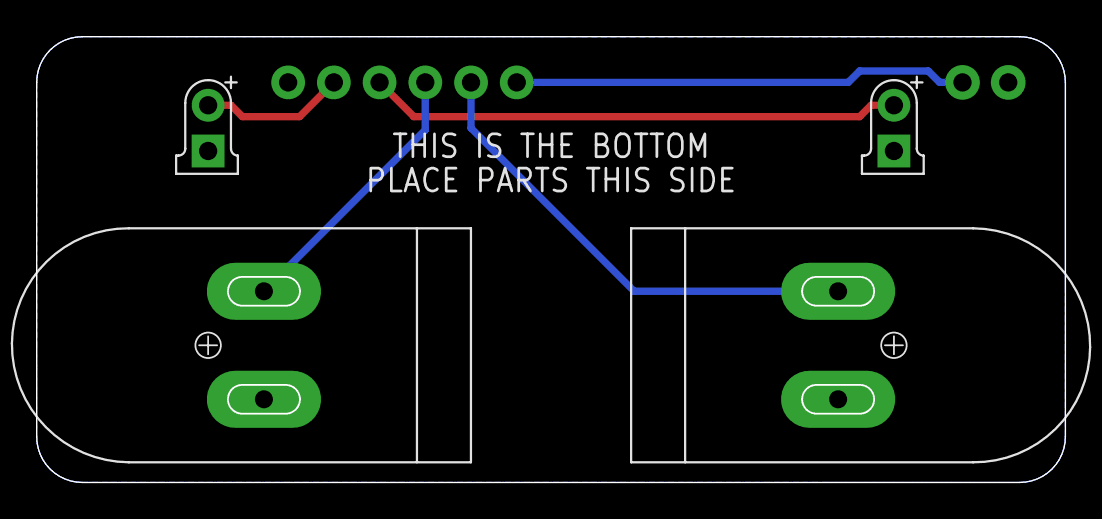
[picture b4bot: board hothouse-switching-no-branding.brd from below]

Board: 2 copper layers, 57.1 x 24.8 mm, 8 parts (2 on the bottom side), 6 nets.

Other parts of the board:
U$1: OSHW-LOGO-M

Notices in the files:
parts and their libraries:
SparkFun-Aesthetics: Licensing: Creative Commons ShareAlike 4.0 International - https://creativecommons.org/licenses/by-sa/4.0
